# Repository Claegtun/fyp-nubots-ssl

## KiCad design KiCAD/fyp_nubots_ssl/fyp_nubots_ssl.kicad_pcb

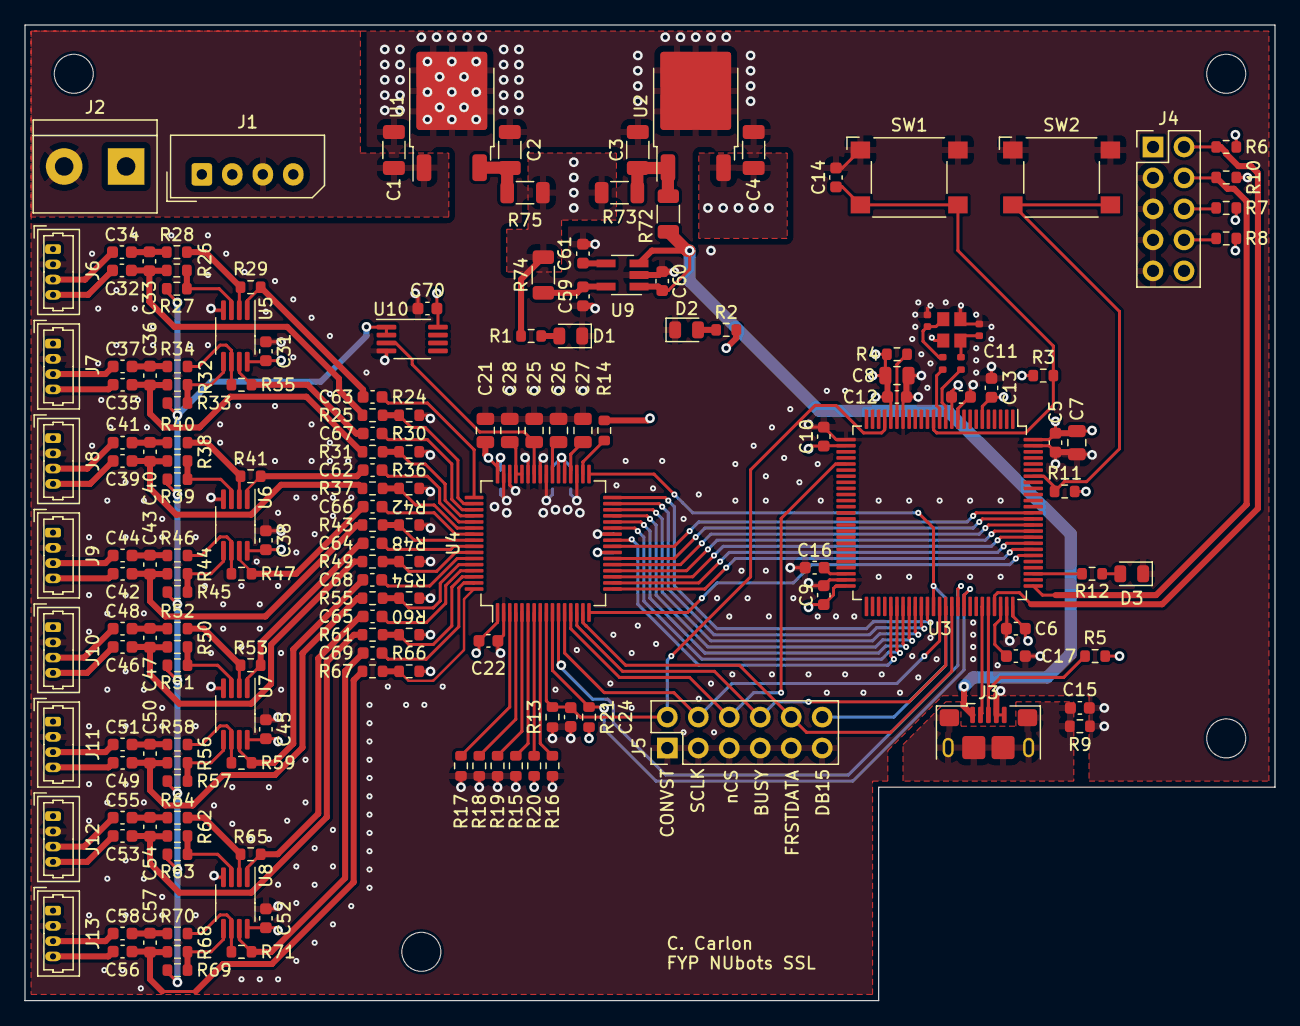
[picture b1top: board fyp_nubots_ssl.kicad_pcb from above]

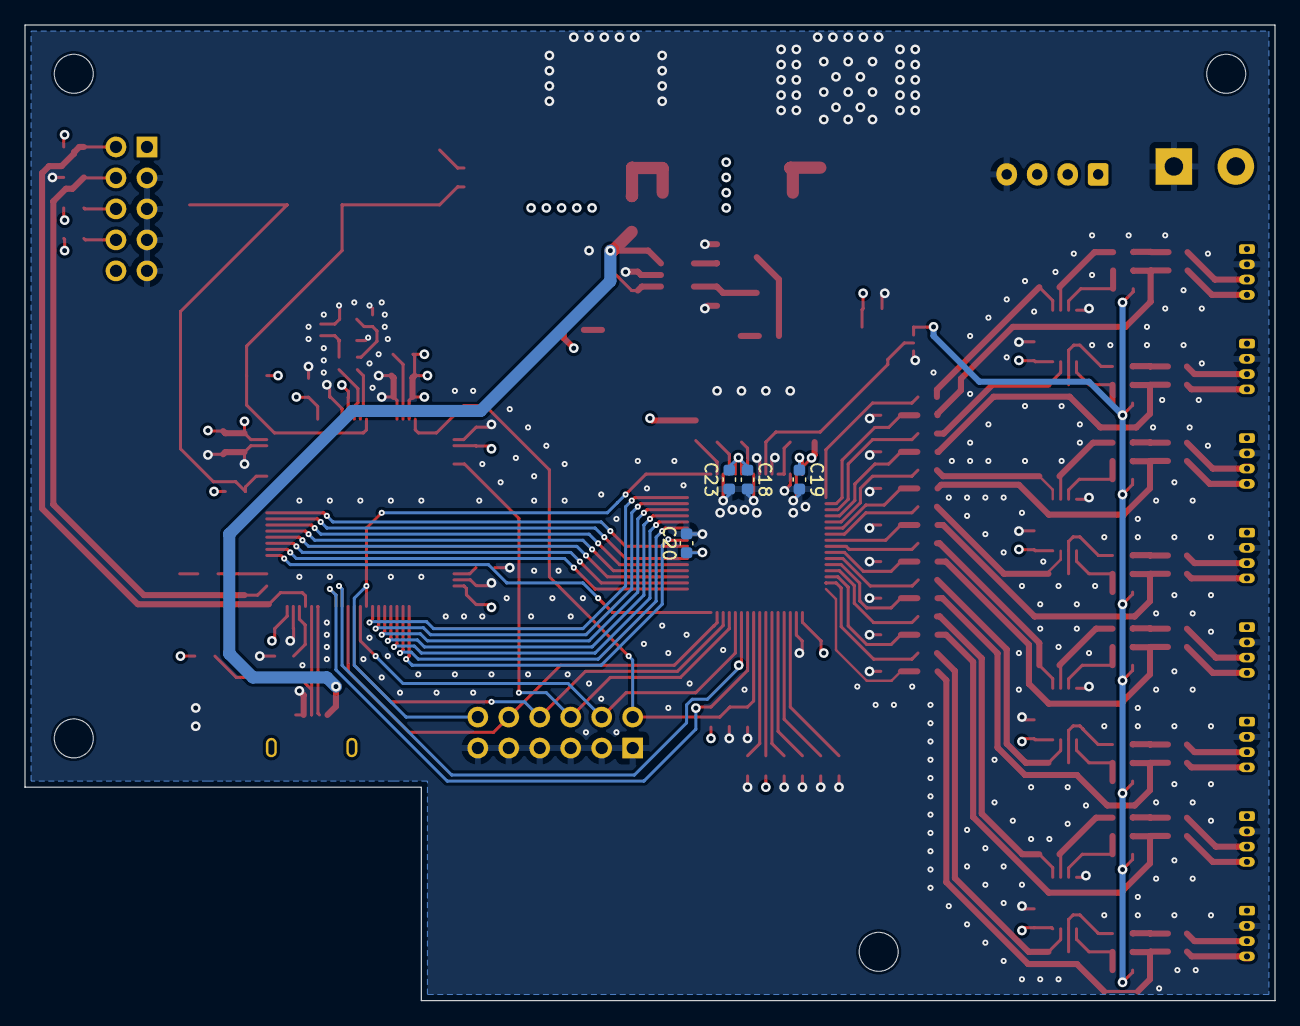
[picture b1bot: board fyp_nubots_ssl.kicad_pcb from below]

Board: 4 copper layers, 102.5 x 80.0 mm, 174 parts (4 on the bottom side), 136 nets.

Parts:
C1, C3: 0.33μF; C_1206_3216Metric
C2, C4: 0.1μF; C_1206_3216Metric
C5, C6, C9, C10, C11, C12, C13, C14, C16, C17, C18, C19, C20, C22, C23, C31, C32, C33, C34, C35, C36, C37, C38, C39, C40, C41, C42, C43, C44, C45, C46, C47, C48, C49, C50, C51, C52, C53, C54, C55, C56, C57, C58, C62, C63, C64, C65, C66, C67, C68, C69, C70: 100n; C_0603_1608Metric
C7: 4.7μ; C_0805_2012Metric
C8, C26, C27: 1μ; C_0805_2012Metric
C15: 4.7n; C_0603_1608Metric
C21, C28: 10μ; C_0805_2012Metric
C24: 4.7p; C_0603_1608Metric
C25: 100n; C_0805_2012Metric
C29, C30: 5.6p; C_0402_1005Metric
C59, C60: 1μ; C_0603_1608Metric
C61: 10n; C_0603_1608Metric
D1, D2, D3: LED; LED_0805_2012Metric
J1: Conn_01x04_Pin; Molex_SPOX_5267-04A_1x04_P2.50mm_Vertical
J2: Screw_Terminal_01x02; TerminalBlock_bornier-2_P5.08mm
J3: USB_B_Micro; USB_Micro-B_Amphenol_10118193-0001LF_Horizontal
J4: Conn_02x05_Odd_Even; PinHeader_2x05_P2.54mm_Vertical
J5: Conn_02x06_Odd_Even; PinHeader_2x06_P2.54mm_Vertical
J6, J7, J8, J9, J10, J11, J12, J13: Conn_01x04_Pin; Molex_PicoBlade_53047-0410_1x04_P1.25mm_Vertical
R1, R5: 1.5k; R_0603_1608Metric
R2, R12: 650; R_0603_1608Metric
R3, R6, R7, R8, R10, R11, R13, R14, R15, R16, R17, R18, R19, R20, R21: 10k; R_0603_1608Metric
R4: 47; R_0603_1608Metric
R9: 1M; R_0603_1608Metric
R22, R23: 0; R_0402_1005Metric
R24, R25, R30, R31, R36, R37, R42, R43, R48, R49, R54, R55, R60, R61, R66, R67: 0; R_0603_1608Metric
R26, R27, R28, R29, R32, R33, R34, R35, R38, R39, R40, R41, R44, R45, R46, R47, R50, R51, R52, R53, R56, R57, R58, R59, R62, R63, R64, R65, R68, R69, R70, R71: 5k; R_0603_1608Metric
R72, R73, R74, R75: 0; R_1206_3216Metric
SW1, SW2: SW_Omron_B3FS; SW_SPST_Omron_B3FS-100xP
U1: L78M05; TO-252-2
U2: UA78M33; TO-252-2
U3: STM32H723VGTx; LQFP-100_14x14mm_P0.5mm
U4: AD7606; LQFP-64_10x10mm_P0.5mm
U5, U6, U7, U8, U10: TLV272; MSOP-8_3x3mm_P0.65mm
U9: LD3985M18R_SOT23; SOT-23-5_HandSoldering
Y1: Crystal_GND24; Crystal_SMD_2520-4Pin_2.5x2.0mm

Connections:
+3V3: C4.2, C5.1, C6.1, C7.1, C8.1, C9.1, C10.1, C11.1, C12.1, C13.1, C20.1, J4.1, R2.2, R3.1, R4.2, R5.1, R6.1, R7.1, R8.1, R11.1, R14.2, R20.2, R21.2, U2.3 (OUT), U3.6 (VBAT), U3.11 (VDD), U3.21 (VDDA), U3.27 (VDD), U3.50 (VDD), U3.75 (VDD), U3.100 (VDD), U4.23 (Vdrive)
+5V: C18.1, C19.1, C21.1, C22.1, C23.1, C31.1, C38.1, C45.1, C52.1, C70.1, J6.1, J7.1, J8.1, J9.1, J10.1, J11.1, J12.1, J13.1, R1.2, R73.1, R74.2, R75.2, U4.1 (AVCC), U4.37 (AVCC), U4.38 (AVCC), U4.48 (AVCC), U5.8 (V+), U6.8 (V+), U7.8 (V+), U8.8 (V+), U10.8 (V+)
+5VD: C60.2, J3.1 (VBUS), R72.1, U9.1 (VIN), U9.3 (INH)
/V_IN: C1.2, J1.3, J2.2, U1.1 (IN)
/analogue/BUSY: J5.8, U3.64 (PC7), U4.14 (BUSY)
/analogue/CONVST: C24.1, J5.2, R13.2, U3.22 (PA0), U4.9 (CONVST_A)
/analogue/DB0: U3.81 (PD0), U4.16 (DB0)
/analogue/DB1: U3.82 (PD1), U4.17 (DB1)
/analogue/DB2: U3.83 (PD2), U4.18 (DB2)
/analogue/DB3: U3.84 (PD3), U4.19 (DB3)
/analogue/DB4: U3.85 (PD4), U4.20 (DB4)
/analogue/DB5: U3.86 (PD5), U4.21 (DB5)
/analogue/DB6: U3.87 (PD6), U4.22 (DB6)
/analogue/DB7: U3.88 (PD7), U4.24 (DB7/DOUT_A)
/analogue/DB8: U3.55 (PD8), U4.25 (DB8/DOUT_B)
/analogue/DB9: U3.56 (PD9), U4.27 (DB9)
/analogue/DB10: U3.57 (PD10), U4.28 (DB10)
/analogue/DB11: U3.58 (PD11), U4.29 (DB11)
/analogue/DB12: U3.59 (PD12), U4.30 (DB12)
/analogue/DB13: U3.60 (PD13), U4.31 (DB13)
/analogue/DB14: U3.61 (PD14), U4.32 (DB14/HBEN)
/analogue/DB15: J5.12, U3.62 (PD15), U4.33 (DB15/BYTE_SEL)
/analogue/FRSTDATA: J5.10, U3.65 (PC8), U4.15 (FRSTDATA)
/analogue/REF: R27.2, R33.2, R39.2, R45.2, R51.2, R57.2, R63.2, R69.2, U10.1, U10.2 (-)
/analogue/REFOUT: C25.1, U4.42 (REFIN/REFOUT), U10.3 (+)
/analogue/RESET: U3.66 (PC9), U4.11 (RESET)
/analogue/SCLK: J5.4, U3.63 (PC6), U4.12 (~RD/SCLK)
/analogue/channels_12/CH1+: C63.2, U4.49 (V1)
/analogue/channels_12/CH1-: R24.2, R25.2, U4.50 (V1GND)
/analogue/channels_12/CH2+: C67.2, U4.51 (V2)
/analogue/channels_12/CH2-: R30.2, R31.2, U4.52 (V2GND)
/analogue/channels_12/xCH1+: C34.1, J6.3
/analogue/channels_12/xCH1-: C32.1, J6.4
/analogue/channels_12/xCH2+: C37.1, J7.3
/analogue/channels_12/xCH2-: C35.1, J7.4
/analogue/channels_34/CH1+: C62.2, U4.53 (V3)
/analogue/channels_34/CH1-: R36.2, R37.2, U4.54 (V3GND)
/analogue/channels_34/CH2+: C66.2, U4.55 (V4)
/analogue/channels_34/CH2-: R42.2, R43.2, U4.56 (V4GND)
/analogue/channels_34/xCH1+: C41.1, J8.3
/analogue/channels_34/xCH1-: C39.1, J8.4
/analogue/channels_34/xCH2+: C44.1, J9.3
/analogue/channels_34/xCH2-: C42.1, J9.4
/analogue/channels_56/CH1+: C64.2, U4.57 (V5)
/analogue/channels_56/CH1-: R48.2, R49.2, U4.58 (V5GND)
/analogue/channels_56/CH2+: C68.2, U4.59 (V6)
/analogue/channels_56/CH2-: R54.2, R55.2, U4.60 (V6GND)
/analogue/channels_56/xCH1+: C48.1, J10.3
/analogue/channels_56/xCH1-: C46.1, J10.4
/analogue/channels_56/xCH2+: C51.1, J11.3
/analogue/channels_56/xCH2-: C49.1, J11.4
/analogue/channels_78/CH1+: C65.2, U4.61 (V7)
/analogue/channels_78/CH1-: R60.2, R61.2, U4.62 (V7GND)
/analogue/channels_78/CH2+: C69.2, U4.63 (V8)
/analogue/channels_78/CH2-: R66.2, R67.2, U4.64 (V8GND)
/analogue/channels_78/xCH1+: C55.1, J12.3
/analogue/channels_78/xCH1-: C53.1, J12.4
/analogue/channels_78/xCH2+: C58.1, J13.3
/analogue/channels_78/xCH2-: C56.1, J13.4
/analogue/nCS: J5.6, U3.30 (PA6), U4.13 (~CS)
/analogue/nWR: R21.1, U3.67 (PA8), U4.10 (CONVST_B)
/processor/BOOT: R11.2, SW2.2, U3.94 (BOOT0)
/processor/JTCK_SWCLK: J4.4, R10.1, U3.76 (PA14(JTCK)
/processor/JTDI: J4.8, R8.2
/processor/JTDO_SWO: J4.6, R7.2
/processor/JTMS_SWDIO: J4.2, R6.2, U3.72 (PA13(JTMS)
/processor/LED_0: R12.2, U3.78 (PC10)
/processor/NRST: C14.1, R3.2, SW1.2, U3.14 (NRST)
/processor/PH0_OSC_IN: R22.2, U3.12 (PH0)
/processor/PH1_OSC_OUT: R23.2, U3.13 (PH1)
/processor/USB_OTG_HS_DM: J3.2 (D-), U3.70 (PA11)
/processor/USB_OTG_HS_DP: J3.3 (D+), R5.2, U3.71 (PA12)
GND: C1.1, C2.1, C3.1, C4.1, C5.2, C6.2, C7.2, C8.2, C9.2, C10.2, C11.2, C12.2, C13.2, C14.2, C15.2, C16.1, C17.2, C18.2, C19.2, C20.2, C21.2, C22.2, C23.2, C24.2, C25.2, C26.1, C27.1, C28.1, C29.2, C30.2, C31.2, C38.2, C45.2, C52.2, C59.1, C60.1, C61.1, C70.2, D1.1 (K), D2.1 (K), D3.1 (K), J1.4, J2.1, J3.4 (ID), J3.5 (GND), J4.3, J4.5, J4.7, J4.9, J5.1, J5.3, J5.5, J5.7, J5.9, J5.11, J6.2, J7.2, J8.2, J9.2, J10.2, J11.2, J12.2, J13.2, R9.2, R10.2, R13.1, R15.1, R16.1, R17.2, R18.2, R19.2, R24.1, R30.1, R36.1, R42.1, R48.1, R54.1, R60.1, R66.1, SW1.1, SW2.1, U1.2 (GND), U2.2 (GND), U3.10 (VSS), U3.19 (VSSA), U3.26 (VSS), U3.49 (VSS), U3.74 (VSS), U3.99 (VSS), U4.2 (AGND), U4.26 (AGND), U4.35 (AGND), U4.40 (AGND), U4.41 (AGND), U4.43 (REFGND), U4.46 (REFGND), U4.47 (AGND), U5.4 (V-), U6.4 (V-), U7.4 (V-), U8.4 (V-), U9.2 (GND), U10.4 (V-), Y1.2, Y1.4
unnamed: C16.2, U3.48 (VCAP)
unnamed: C17.1, U3.73 (VCAP)
unnamed: C26.2, U4.39 (REGCAP)
unnamed: C27.2, U4.36 (REGCAP)
unnamed: C29.1, R22.1, Y1.1
unnamed: C30.1, R23.1, Y1.3
unnamed: C32.2, C33.2, R25.1, R26.1
unnamed: C33.1, C34.2, R28.1
unnamed: C35.2, C36.2, R31.1, R32.1
unnamed: C36.1, C37.2, R34.1
unnamed: C39.2, C40.2, R37.1, R38.1
unnamed: C40.1, C41.2, R40.1
unnamed: C42.2, C43.2, R43.1, R44.1
unnamed: C43.1, C44.2, R46.1
unnamed: C46.2, C47.2, R49.1, R50.1
unnamed: C47.1, C48.2, R52.1
unnamed: C49.2, C50.2, R55.1, R56.1
unnamed: C50.1, C51.2, R58.1
unnamed: C53.2, C54.2, R61.1, R62.1
unnamed: C54.1, C55.2, R64.1
unnamed: C56.2, C57.2, R67.1, R68.1
unnamed: C57.1, C58.2, R70.1
unnamed: C62.1, R41.2, U6.1
unnamed: C63.1, R29.2, U5.1
unnamed: C64.1, R53.2, U7.1
unnamed: C65.1, R65.2, U8.1
unnamed: C66.1, R47.2, U6.7
unnamed: C67.1, R35.2, U5.7
unnamed: C68.1, R59.2, U7.7
unnamed: C69.1, R71.2, U8.7
unnamed: D1.2 (A), R1.1
unnamed: D2.2 (A), R2.1
unnamed: D3.2 (A), R12.1
unnamed: C15.1, J3.6 (Shield), R9.1
unnamed: C2.2, R75.1, U1.3 (OUT)
unnamed: C3.2, R72.2, R73.2, U2.1 (IN)
unnamed: R4.1, U3.20 (VREF+)
unnamed: R17.1, U4.3 (OS0)
unnamed: R18.1, U4.4 (OS1)
unnamed: R19.1, U4.5 (OS2)
unnamed: R16.2, U4.8 (RANGE)
unnamed: C28.2, U4.44 (REFCAPA), U4.45 (REFCAPB)
unnamed: R14.1, U4.34 (REF_SELECT)
unnamed: R15.2, U4.6 (~PAR/SER/BYTE_SEL)
unnamed: R20.1, U4.7 (~STBY)
unnamed: R26.2, R27.1, U5.3 (+)
unnamed: R28.2, R29.1, U5.2 (-)
unnamed: R32.2, R33.1, U5.5 (+)
unnamed: R34.2, R35.1, U5.6 (-)
unnamed: R38.2, R39.1, U6.3 (+)
unnamed: R40.2, R41.1, U6.2 (-)
unnamed: R44.2, R45.1, U6.5 (+)
unnamed: R46.2, R47.1, U6.6 (-)
unnamed: R50.2, R51.1, U7.3 (+)
unnamed: R52.2, R53.1, U7.2 (-)
unnamed: R56.2, R57.1, U7.5 (+)
unnamed: R58.2, R59.1, U7.6 (-)
unnamed: R62.2, R63.1, U8.3 (+)
unnamed: R64.2, R65.1, U8.2 (-)
unnamed: R68.2, R69.1, U8.5 (+)
unnamed: R70.2, R71.1, U8.6 (-)
unnamed: C61.2, U9.4 (BYP)
unnamed: C59.2, R74.1, U9.5 (VOUT)

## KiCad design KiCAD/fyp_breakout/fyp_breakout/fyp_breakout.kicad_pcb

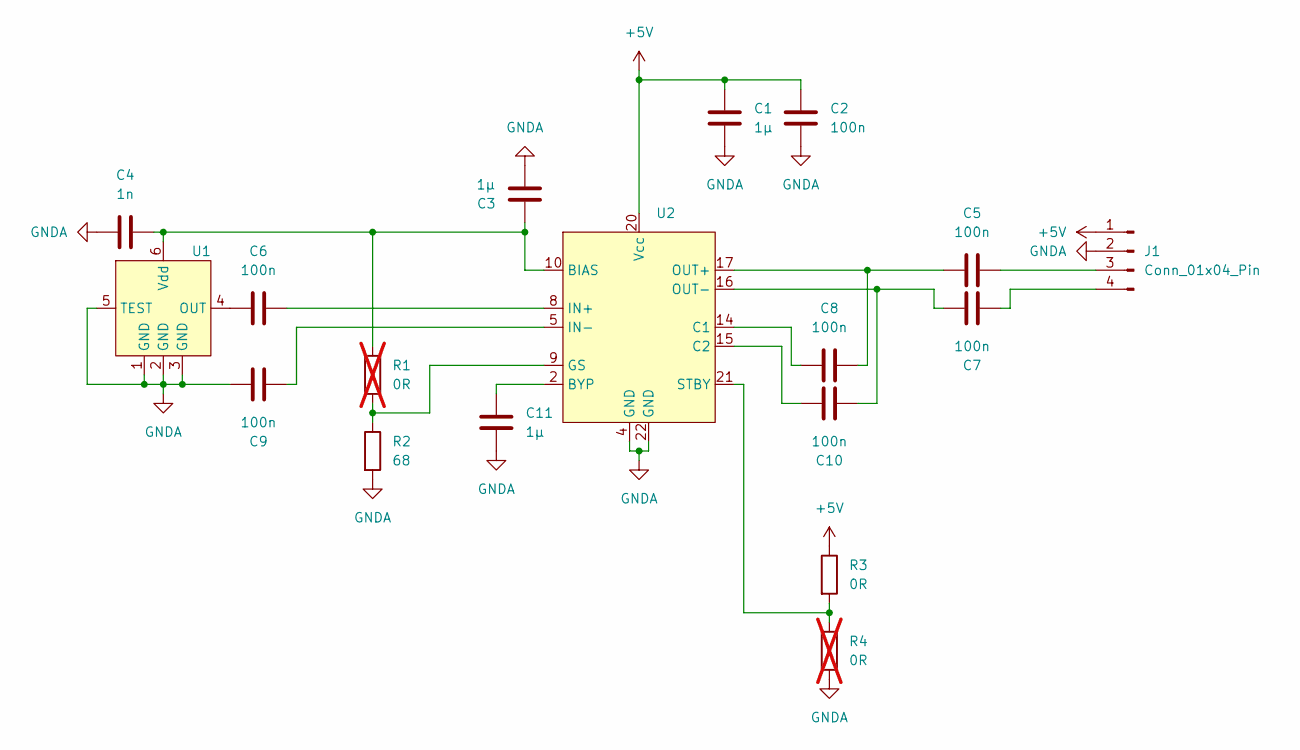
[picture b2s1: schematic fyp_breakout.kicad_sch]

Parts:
C1, C3, C11: 1μ; C_0603_1608Metric
C2, C5, C6, C7, C8, C9, C10: 100n; C_0603_1608Metric
C4: 1n; C_0603_1608Metric
J1: Conn_01x04_Pin; Molex_PicoBlade_53048-0410_1x04_P1.25mm_Horizontal
R1, R4: 0R; C_0603_1608Metric; not fitted
R2: 68; C_0603_1608Metric
R3: 0R; C_0603_1608Metric
U1: SPH1642HT5H-1
U2: QFN-24-1EP_4x4mm_P0.5mm_EP2.6x2.6mm

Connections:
+5V: C1.2, C2.2, J1.1, R3.1, U2.20 (Vcc)
GNDA: C1.1, C2.1, C3.1, C4.1, C9.1, C11.2, J1.2, R2.2, R4.1, U1.1 (GND), U1.2 (GND), U1.3 (GND), U1.5 (TEST), U2.4 (GND), U2.22 (GND)
unnamed: C5.2, J1.3
unnamed: C7.2, J1.4
unnamed: C6.1, U1.4 (OUT)
unnamed: C3.2, C4.2, R1.1, U1.6 (Vdd), U2.10 (BIAS)
unnamed: C11.1, U2.2 (BYP)
unnamed: C8.1, U2.14 (C1)
unnamed: C10.1, U2.15 (C2)
unnamed: R1.2, R2.1, U2.9 (GS)
unnamed: C6.2, U2.8 (IN+)
unnamed: C9.2, U2.5 (IN-)
unnamed: C5.1, C8.2, U2.17 (OUT+)
unnamed: C7.1, C10.2, U2.16 (OUT-)
unnamed: R3.2, R4.2, U2.21 (STBY)

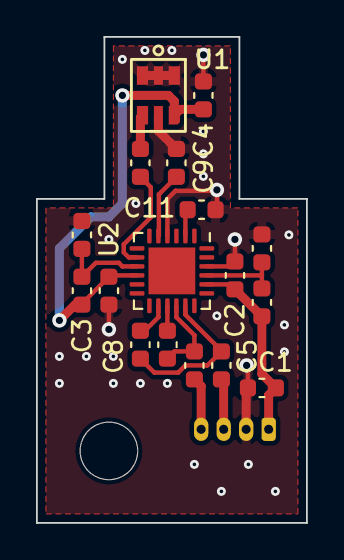
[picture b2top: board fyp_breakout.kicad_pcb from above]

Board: 2 copper layers, 15.0 x 27.0 mm, 18 parts (1 on the bottom side), 15 nets.

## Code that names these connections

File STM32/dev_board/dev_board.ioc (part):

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Mcu.Name=STM32H723ZGTx
Mcu.Package=LQFP144
Mcu.UserName=STM32H723ZGTx
PA0.Signal=S_TIM5_CH1
PA1.GPIOParameters=GPIO_Label
PA1.GPIO_Label=RMII_REF_CLK
PA1.Mode=RMII
PA1.Signal=ETH_REF_CLK
PA10.GPIOParameters=GPIO_Label
PA10.GPIO_Label=USB_FS_ID
PA10.Mode=OTG/Dual-Role-Device-FS
PA10.Signal=USB_OTG_HS_ID
PA11.GPIOParameters=GPIO_Label
PA11.GPIO_Label=USB_FS_DM
PA11.Mode=OTG/Dual-Role-Device-FS
PA11.Signal=USB_OTG_HS_DM
PA12.GPIOParameters=GPIO_Label
PA12.GPIO_Label=USB_FS_DP
PA12.Mode=OTG/Dual-Role-Device-FS
PA12.Signal=USB_OTG_HS_DP
PA13(JTMS/SWDIO).GPIOParameters=GPIO_Label
PA13(JTMS/SWDIO).GPIO_Label=SWDIO
PA13(JTMS/SWDIO).Mode=Trace_Asynchronous_SW
PA13(JTMS/SWDIO).Signal=DEBUG_JTMS-SWDIO
PA14(JTCK/SWCLK).GPIOParameters=GPIO_Label
PA14(JTCK/SWCLK).GPIO_Label=SWCLK
PA14(JTCK/SWCLK).Mode=Trace_Asynchronous_SW
PA14(JTCK/SWCLK).Signal=DEBUG_JTCK-SWCLK
PA15(JTDI).Signal=S_TIM2_CH1_ETR
PA2.GPIOParameters=GPIO_Label
PA2.GPIO_Label=RMII_MDIO
PA2.Mode=RMII
PA2.Signal=ETH_MDIO
PA3.GPIOParameters=GPIO_Label
PA3.GPIO_Label=ADC_CNVST
PA3.Signal=GPIO_Output
PA4.Mode=NSS_Signal_Hard_Input
PA4.Signal=SPI3_NSS
PA5.Mode=Full_Duplex_Slave
PA5.Signal=SPI1_SCK
PA7.GPIOParameters=GPIO_Label
PA7.GPIO_Label=RMII_CRS_DV
PA7.Mode=RMII
PA7.Signal=ETH_CRS_DV
PA8.Signal=S_TIM1_CH1
PA9.GPIOParameters=GPIO_Label
PA9.GPIO_Label=USB_FS_VBUS
PA9.Mode=Activate_VBUS_FS
PA9.Signal=USB_OTG_HS_VBUS
PB0.GPIOParameters=GPIO_Label
PB0.GPIO_Label=LED_GREEN
PB0.Signal=GPIO_Output
PB10.Mode=RX_Only_Simplex_Unidirect_Slave
PB10.Signal=SPI2_SCK
PB12.Mode=NSS_Signal_Hard_Input
PB12.Signal=SPI2_NSS
PB13.GPIOParameters=GPIO_Label
PB13.GPIO_Label=RMII_TXD1
PB13.Mode=RMII
PB13.Signal=ETH_TXD1
PB14.GPIOParameters=GPIO_Label
PB14.GPIO_Label=LED_RED
PB14.Signal=GPIO_Output
PB2.Mode=RX_Only_Simplex_Unidirect_Slave
PB2.Signal=SPI3_MOSI
PB3(JTDO/TRACESWO).GPIOParameters=GPIO_Label
PB3(JTDO/TRACESWO).GPIO_Label=SWO
PB3(JTDO/TRACESWO).Mode=Trace_Asynchronous_SW
PB3(JTDO/TRACESWO).Signal=DEBUG_JTDO-SWO
PB4(NJTRST).Signal=S_TIM3_CH1
PB5.Mode=Full_Duplex_Slave
PB5.Signal=SPI1_MOSI
PB8.GPIOParameters=GPIO_Label
PB8.GPIO_Label=ADC_RESET
PB8.Signal=GPIO_Output
PC1.GPIOParameters=GPIO_Label
PC1.GPIO_Label=RMII_MDC
PC1.Mode=RMII
PC1.Signal=ETH_MDC
PC10.Mode=RX_Only_Simplex_Unidirect_Slave
PC10.Signal=SPI3_SCK
PC13.GPIOParameters=GPIO_Label
PC13.GPIO_Label=B1 (Blue_User_Button)
PC13.Signal=GPIO_Input
PC14-OSC32_IN.Mode=LSE-External-Oscillator
PC14-OSC32_IN.Signal=RCC_OSC32_IN
PC15-OSC32_OUT.Mode=LSE-External-Oscillator
PC15-OSC32_OUT.Signal=RCC_OSC32_OUT
PC3_C.Mode=RX_Only_Simplex_Unidirect_Slave
PC3_C.Signal=SPI2_MOSI
PC4.GPIOParameters=GPIO_Label
PC4.GPIO_Label=RMII_RXD0
PC4.Mode=RMII
PC4.Signal=ETH_RXD0
PC5.GPIOParameters=GPIO_Label
PC5.GPIO_Label=RMII_RXD1
PC5.Mode=RMII
PC5.Signal=ETH_RXD1
PC6.Signal=S_TIM8_CH1
PD10.GPIOParameters=GPIO_Label
PD10.GPIO_Label=USB_FS_PWR_EN
PD10.Signal=GPIO_Output
PD14.GPIOParameters=GPIO_Label,GPIO_ModeDefaultEXTI
PD14.GPIO_Label=ADC_BUSY
PD14.GPIO_ModeDefaultEXTI=GPIO_MODE_IT_FALLING
PD14.Signal=GPXTI14
PD8.GPIOParameters=GPIO_Label
PD8.GPIO_Label=STLK_VCP_RX
PD8.Mode=Asynchronous
PD8.Signal=USART3_TX
PD9.GPIOParameters=GPIO_Label
PD9.GPIO_Label=STLK_VCP_TX
PD9.Mode=Asynchronous
PD9.Signal=USART3_RX
PE1.GPIOParameters=GPIO_Label
PE1.GPIO_Label=LED_YELLOW
PE1.Signal=GPIO_Output
PE2.Mode=RX_Only_Simplex_Unidirect_Slave
PE2.Signal=SPI4_SCK
PE4.Mode=NSS_Signal_Hard_Input
PE4.Signal=SPI4_NSS
PE6.Mode=RX_Only_Simplex_Unidirect_Slave
PE6.Signal=SPI4_MOSI
PF4.GPIOParameters=GPIO_Label
PF4.GPIO_Label=SIG_0
PF4.Signal=GPIO_Output
PG10.Mode=NSS_Signal_Hard_Input
PG10.Signal=SPI1_NSS
PG11.GPIOParameters=GPIO_Label
PG11.GPIO_Label=RMII_TX_EN
PG11.Mode=RMII
PG11.Signal=ETH_TX_EN
PG13.GPIOParameters=GPIO_Label
PG13.GPIO_Label=RMII_TXD0
PG13.Mode=RMII
PG13.Signal=ETH_TXD0
PG7.GPIOParameters=GPIO_Label
PG7.GPIO_Label=USB_FS_OVCR
PG7.Signal=GPXTI7
PG9.Mode=Full_Duplex_Slave
PG9.Signal=SPI1_MISO
PH0-OSC_IN.GPIOParameters=GPIO_Label
PH0-OSC_IN.GPIO_Label=MCO
PH0-OSC_IN.Mode=HSE-External-Clock-Source
PH0-OSC_IN.Signal=RCC_OSC_IN
PH1-OSC_OUT.Signal=RCC_OSC_OUT
RCC.HSE_VALUE=8000000
RCC.SYSCLKFreq_VALUE=550000000
RCC.SYSCLKSource=RCC_SYSCLKSOURCE_PLLCLK
board=NUCLEO-H723ZG
boardIOC=true

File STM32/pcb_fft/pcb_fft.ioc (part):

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Mcu.Name=STM32H723VGTx
Mcu.Package=LQFP100
Mcu.UserName=STM32H723VGTx
PA0.Signal=S_TIM2_CH1_ETR
PA11.Mode=Device_Only_FS
PA11.Signal=USB_OTG_HS_DM
PA12.Mode=Device_Only_FS
PA12.Signal=USB_OTG_HS_DP
PA13(JTMS/SWDIO).Mode=Serial_Wire
PA13(JTMS/SWDIO).Signal=DEBUG_JTMS-SWDIO
PA14(JTCK/SWCLK).Mode=Serial_Wire
PA14(JTCK/SWCLK).Signal=DEBUG_JTCK-SWCLK
PA6.Signal=S_TIM3_CH1
PA9.Mode=Activate_VBUS_FS
PA9.Signal=USB_OTG_HS_VBUS
PC10.GPIOParameters=GPIO_Label
PC10.GPIO_Label=LED_0
PC10.Signal=GPIO_Output
PC6.Signal=S_TIM8_CH1
PC8.GPIOParameters=GPIO_Label
PC8.GPIO_Label=ADC_FRSTDATA
PC8.Signal=GPIO_Input
PC9.GPIOParameters=GPIO_Label
PC9.GPIO_Label=ADC_RESET
PC9.Signal=GPIO_Output
RCC.SYSCLKFreq_VALUE=550000000
RCC.SYSCLKSource=RCC_SYSCLKSOURCE_PLLCLK
board=custom

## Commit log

2023-04-17 Written most of the literature review.
2023-04-27 Began a review of MUSIC.
2023-04-29 Wrote an overview of MUSIC.
2023-04-30 Wrote the table of methods.
2023-05-06 Added figures for the literature review; played around with PRA.
2023-05-28 Added Python simulations.
2023-05-31 Reorganised the Python code for testing and plotting.
2023-06-06 Added SRP-PHAT example.
2023-06-06 Completed the version submitted to Canvas.
2023-07-21 Updated everything for new computer.
2023-08-07 Began the thesis; wrote more simulations for SRP-PHAT; rewrote the section on beamforming.
2023-08-07 Rearranged folders under pryamid_robot; added more initial conditions to iterate therefrom for the pyramid-robot.
2023-08-07 Rearranged the folders under srp_phat; added more simulations for a whistle, maps, etc.
2023-08-07 Made a script to preview .wav files for troubleshooting.
2023-09-04 Began simulations on the frequency and geometry.
2023-09-04 Began the electronics design.
2023-10-28 Submitted final report.
2023-11-03 Did a partially working prototype.
